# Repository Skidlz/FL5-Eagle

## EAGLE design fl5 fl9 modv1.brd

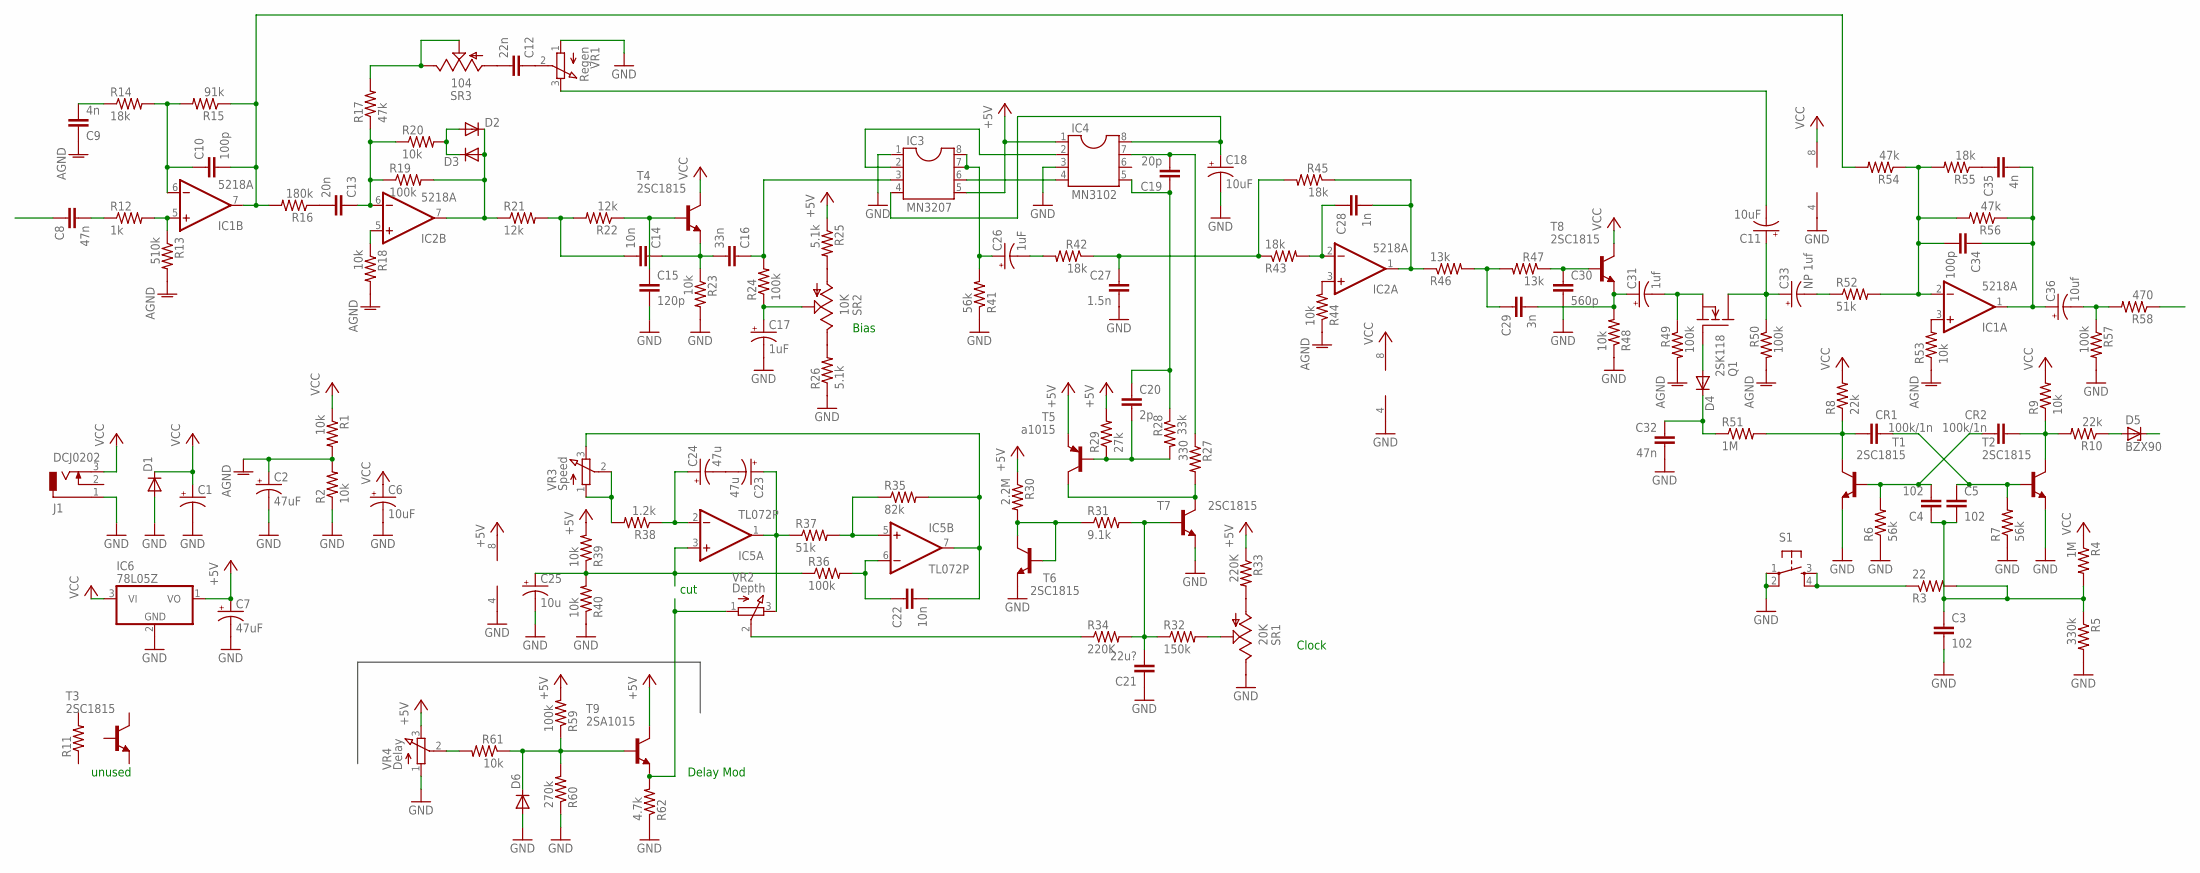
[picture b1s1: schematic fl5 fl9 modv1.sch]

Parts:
C1: CPOL-USE3.5-8; E3,5-8
C2, C7: 47uF; E1,8-4
C3, C4, C5: 102; C025-024X044
C6, C11, C18: 10uF; E1,8-4
C8, C32: 47n; C050-025X075
C9, C35: 4n; C050-025X075
C10, C34: 100p; C025-024X044
C12: 22n; C050-025X075
C13: 20n; C050-025X075
C14, C22: 10n; C050-025X075
C15: 120p; C050-024X044
C16: 33n; C050-025X075
C17, C26: 1uF; E1,8-4
C19: 20p; C025-024X044
C20: 2p; C025-024X044
C21: 22u?; C025-024X044
C23, C24: 47u; E2,5-7
C25: 10u; E1,8-4
C27: 1.5n; C050-025X075
C28: 1n; C050-025X075
C29: 3n; C050-025X075
C30: 560p; C050-024X044
C31: 1uf; E1,8-4
C33: NP 1uf; E1,8-4
C36: 10uf; E1,8-4
CR1, CR2: 100k/1n; C025-024X044
D1: DIODE-C1702-05; C1702-05
D2, D3, D4, D6: DIODE-D-5; D-5
D5: BZX90; DO34Z7
IC1, IC2: 5218A; DIL08
IC3: MN3207; DIL08
IC4: MN3102; DIL08
IC5: TL072P; DIL08
IC6: 78L05Z; TO92
J1: DCJ0202
Q1: 2SK118; TO237
R1, R2, R9, R18, R20, R23, R39, R40, R44, R48, R53, R61: 10k; 0204/5
R3: 22; 0204/5
R4, R51: 1M; 0204/5
R5: 330k; 0204/5
R6, R7, R41: 56k; 0204/5
R8, R10: 22k; 0204/5
R11: R-US_0204/5; 0204/5
R12: 1k; 0204/5
R13: 510k; 0204/5
R14, R42, R43, R45, R55: 18k; 0204/5
R15: 91k; 0204/5
R16: 180k; 0204/5
R17, R54, R56: 47k; 0204/5
R19, R24, R36, R49, R50, R57, R59: 100k; 0204/5
R21, R22: 12k; 0204/5
R25, R26: 5.1k; 0204/5
R27: 330; 0204/5
R28: 33k; 0204/5
R29: 27k; 0204/5
R30: 2.2M; 0204/5
R31: 9.1k; 0204/5
R32: 150k; 0204/5
R33, R34: 220K; 0204/5
R35: 82k; 0204/5
R37, R52: 51k; 0204/5
R38: 1.2k; 0204/5
R46, R47: 13k; 0204/5
R58: 470; 0204/5
R60: 270k; 0204/5
R62: 4.7k; 0204/5
S1: TAC_SWITCHPTH; TACTILE-PTH
SR1: 20K; CA6V
SR2: 10K; CA6V
SR3: 104; CA6V
T1, T2, T3, T4, T6, T7, T8: 2SC1815; TO92-ECB
T5: a1015; TO92-ECB
T9: 2SA1015; TO92-ECB
VR1: Regen; EVUF
VR2: Depth; EVUF
VR3: Speed; EVUF
VR4: Delay; EVUF

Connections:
+5V: C7.+, IC3.5, IC4.1, IC5.8 (V+), IC6.1 (VO), R25.1, R29.2, R30.1, R33.1, R39.2, R59.2, T5.E, T9.C, VR4.3 (E)
AGND: C2.+, C9.1, R1.2, R2.2, R13.2, R18.2, R44.1, R49.2, R50.2, R53.1
GND: C1.-, C2.-, C3.2, C6.-, C7.-, C15.2, C17.-, C18.-, C21.1, C25.-, C27.2, C30.2, C32.2, D1.A, D6.A, IC1.4 (V-), IC2.4 (V-), IC3.1, IC4.3, IC5.4 (V-), IC6.2 (GND), J1.1, R2.1, R5.2, R6.1, R7.1, R23.2, R26.1, R40.1, R41.1, R48.1, R57.2, R60.1, R62.1, S1.1, S1.2, SR1.E, T1.E, T2.E, T6.E, T7.E, VR1.1 (A), VR4.1 (A)
unnamed: CR2.1, R9.1, R10.2, T2.C
unnamed: C5.1, CR1.1, R7.2, T2.B
unnamed: IC1.5 (+IN), R12.2, R13.1
unnamed: C10.2, IC1.7 (OUT), R15.1, R16.2, R54.2
unnamed: C10.1, IC1.6 (-IN), R14.2, R15.2
unnamed: D2.A, D3.C, R20.2
unnamed: D2.C, D3.A, IC2.7 (OUT), R19.2, R21.1
unnamed: C13.1, IC2.6 (-IN), R17.1, R19.1, R20.1
unnamed: C15.1, R22.1, T4.B
unnamed: C3.1, C4.1, C5.2, R3.2, R4.2, R5.1
unnamed: R3.1, S1.3, S1.4
unnamed: R27.2, T5.C, T7.C
unnamed: C4.2, CR2.2, R6.2, T1.B
unnamed: C12.1, VR1.2 (S)
unnamed: IC2.5 (+IN), R18.1
unnamed: R30.2, R31.1, T6.B, T6.C
unnamed: R34.1, VR2.2 (S)
unnamed: IC2.3 (+IN), R44.2
unnamed: C21.2, R31.2, R32.1, R34.2, T7.B
unnamed: C8.2, R12.1
unnamed: R32.2, SR1.S
unnamed: C12.2, SR3.A
unnamed: R33.2, SR1.A
unnamed: C20.2, R28.2, R29.1, T5.B
unnamed: C23.+, IC5.1 (OUT), R37.1, VR2.3 (E)
unnamed: C25.+, IC5.3 (+IN), R36.1, R39.1, R40.2
unnamed: R38.2, VR3.1 (A), VR3.2 (S)
unnamed: C24.+, IC5.2 (-IN), R38.1
unnamed: C22.2, IC5.7 (OUT), R35.2, VR3.3 (E)
unnamed: IC5.5 (+IN), R35.1, R37.2
unnamed: C22.1, IC5.6 (-IN), R36.2
unnamed: C28.1, IC2.2 (-IN), R43.2
unnamed: C28.2, IC2.1 (OUT), R45.1, R46.1
unnamed: C29.1, R46.2, R47.2
unnamed: R17.2, SR3.E, SR3.S
unnamed: C13.2, R16.1
unnamed: C14.2, R21.2, R22.2
unnamed: C14.1, C16.2, R23.1, T4.E
unnamed: C9.2, R14.1
unnamed: R26.2, SR2.E
unnamed: R25.2, SR2.A
unnamed: CR1.2, R8.1, R51.2, T1.C
unnamed: C32.1, D4.C, R51.1
unnamed: C17.+, R24.1, SR2.S
unnamed: C18.+, IC3.4, IC4.8
unnamed: C26.+, IC3.7, IC3.8, R41.2
unnamed: C16.1, IC3.3, R24.2
unnamed: IC3.2, IC4.2
unnamed: IC3.6, IC4.4
unnamed: C19.2, IC4.7, R27.1
unnamed: C19.1, C20.1, IC4.5, R28.1
unnamed: C23.-, C24.-
unnamed: C26.-, R42.2
unnamed: C27.1, R42.1, R43.1, R45.2
unnamed: C11.+, C33.+, Q1.1 (D), R50.1
unnamed: C29.2, C31.+, R48.2, T8.E
unnamed: C36.-, R57.1, R58.2
unnamed: C30.1, R47.1, T8.B
unnamed: D4.A, Q1.2 (G)
unnamed: C33.-, R52.1
unnamed: C11.-, VR1.3 (E)
unnamed: C31.-, Q1.3 (S), R49.1
unnamed: C34.1, C35.2, C36.+, IC1.1 (OUT), R56.1
unnamed: IC1.3 (+IN), R53.2
unnamed: C34.2, IC1.2 (-IN), R52.2, R54.1, R55.2, R56.2
unnamed: C35.1, R55.1
unnamed: D5.A, R10.1
unnamed: R62.2, T9.E, VR2.1 (A)
unnamed: D6.C, R59.1, R60.2, R61.1, T9.B
unnamed: R61.2, VR4.2 (S)
VCC: C1.+, C6.+, D1.C, IC1.8 (V+), IC2.8 (V+), IC6.3 (VI), J1.3, R1.1, R4.1, R8.2, R9.2, T4.C, T8.C

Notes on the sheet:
Clock
Bias
unused
cut
Delay Mod

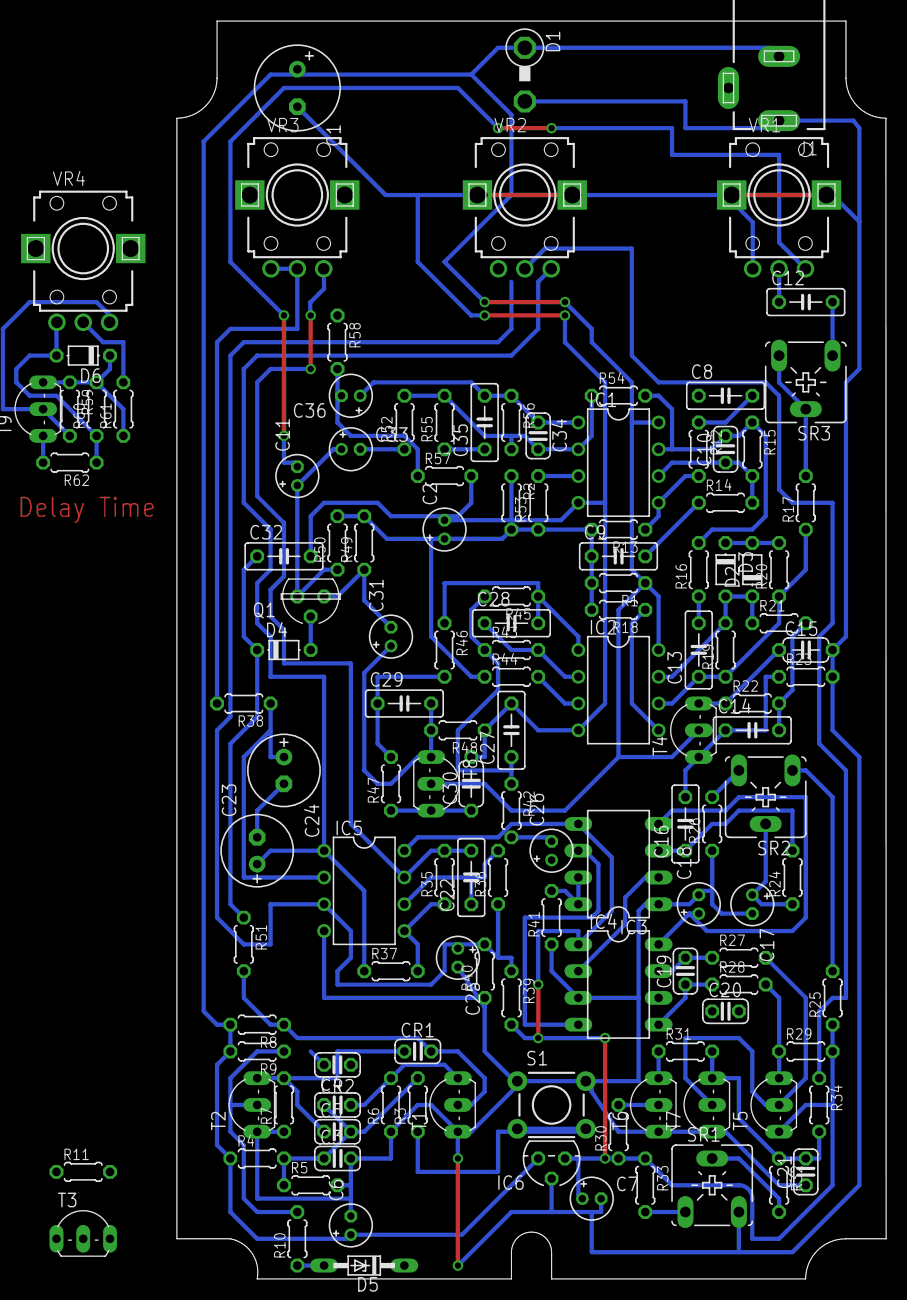
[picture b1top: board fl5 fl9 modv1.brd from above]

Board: 2 copper layers, 67.3 x 119.4 mm, 131 parts (0 on the bottom side), 74 nets.

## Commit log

2015-12-17 :neckbeard: Added .gitattributes & .gitignore files
2015-12-17 First upload

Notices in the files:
parts and their libraries:
SparkFun: Licensing: CC v3.0 Share-Alike You are welcome to use this library for commercial purposes.
